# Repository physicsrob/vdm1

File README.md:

This project contains information on the original VDM-1 (Video Display Module) board manufactured by Processor Technologies, as well as a reproduction board referred to as the VDM-2021.

Visit the docs [Here](https://physicsrob.github.io/vdm1)

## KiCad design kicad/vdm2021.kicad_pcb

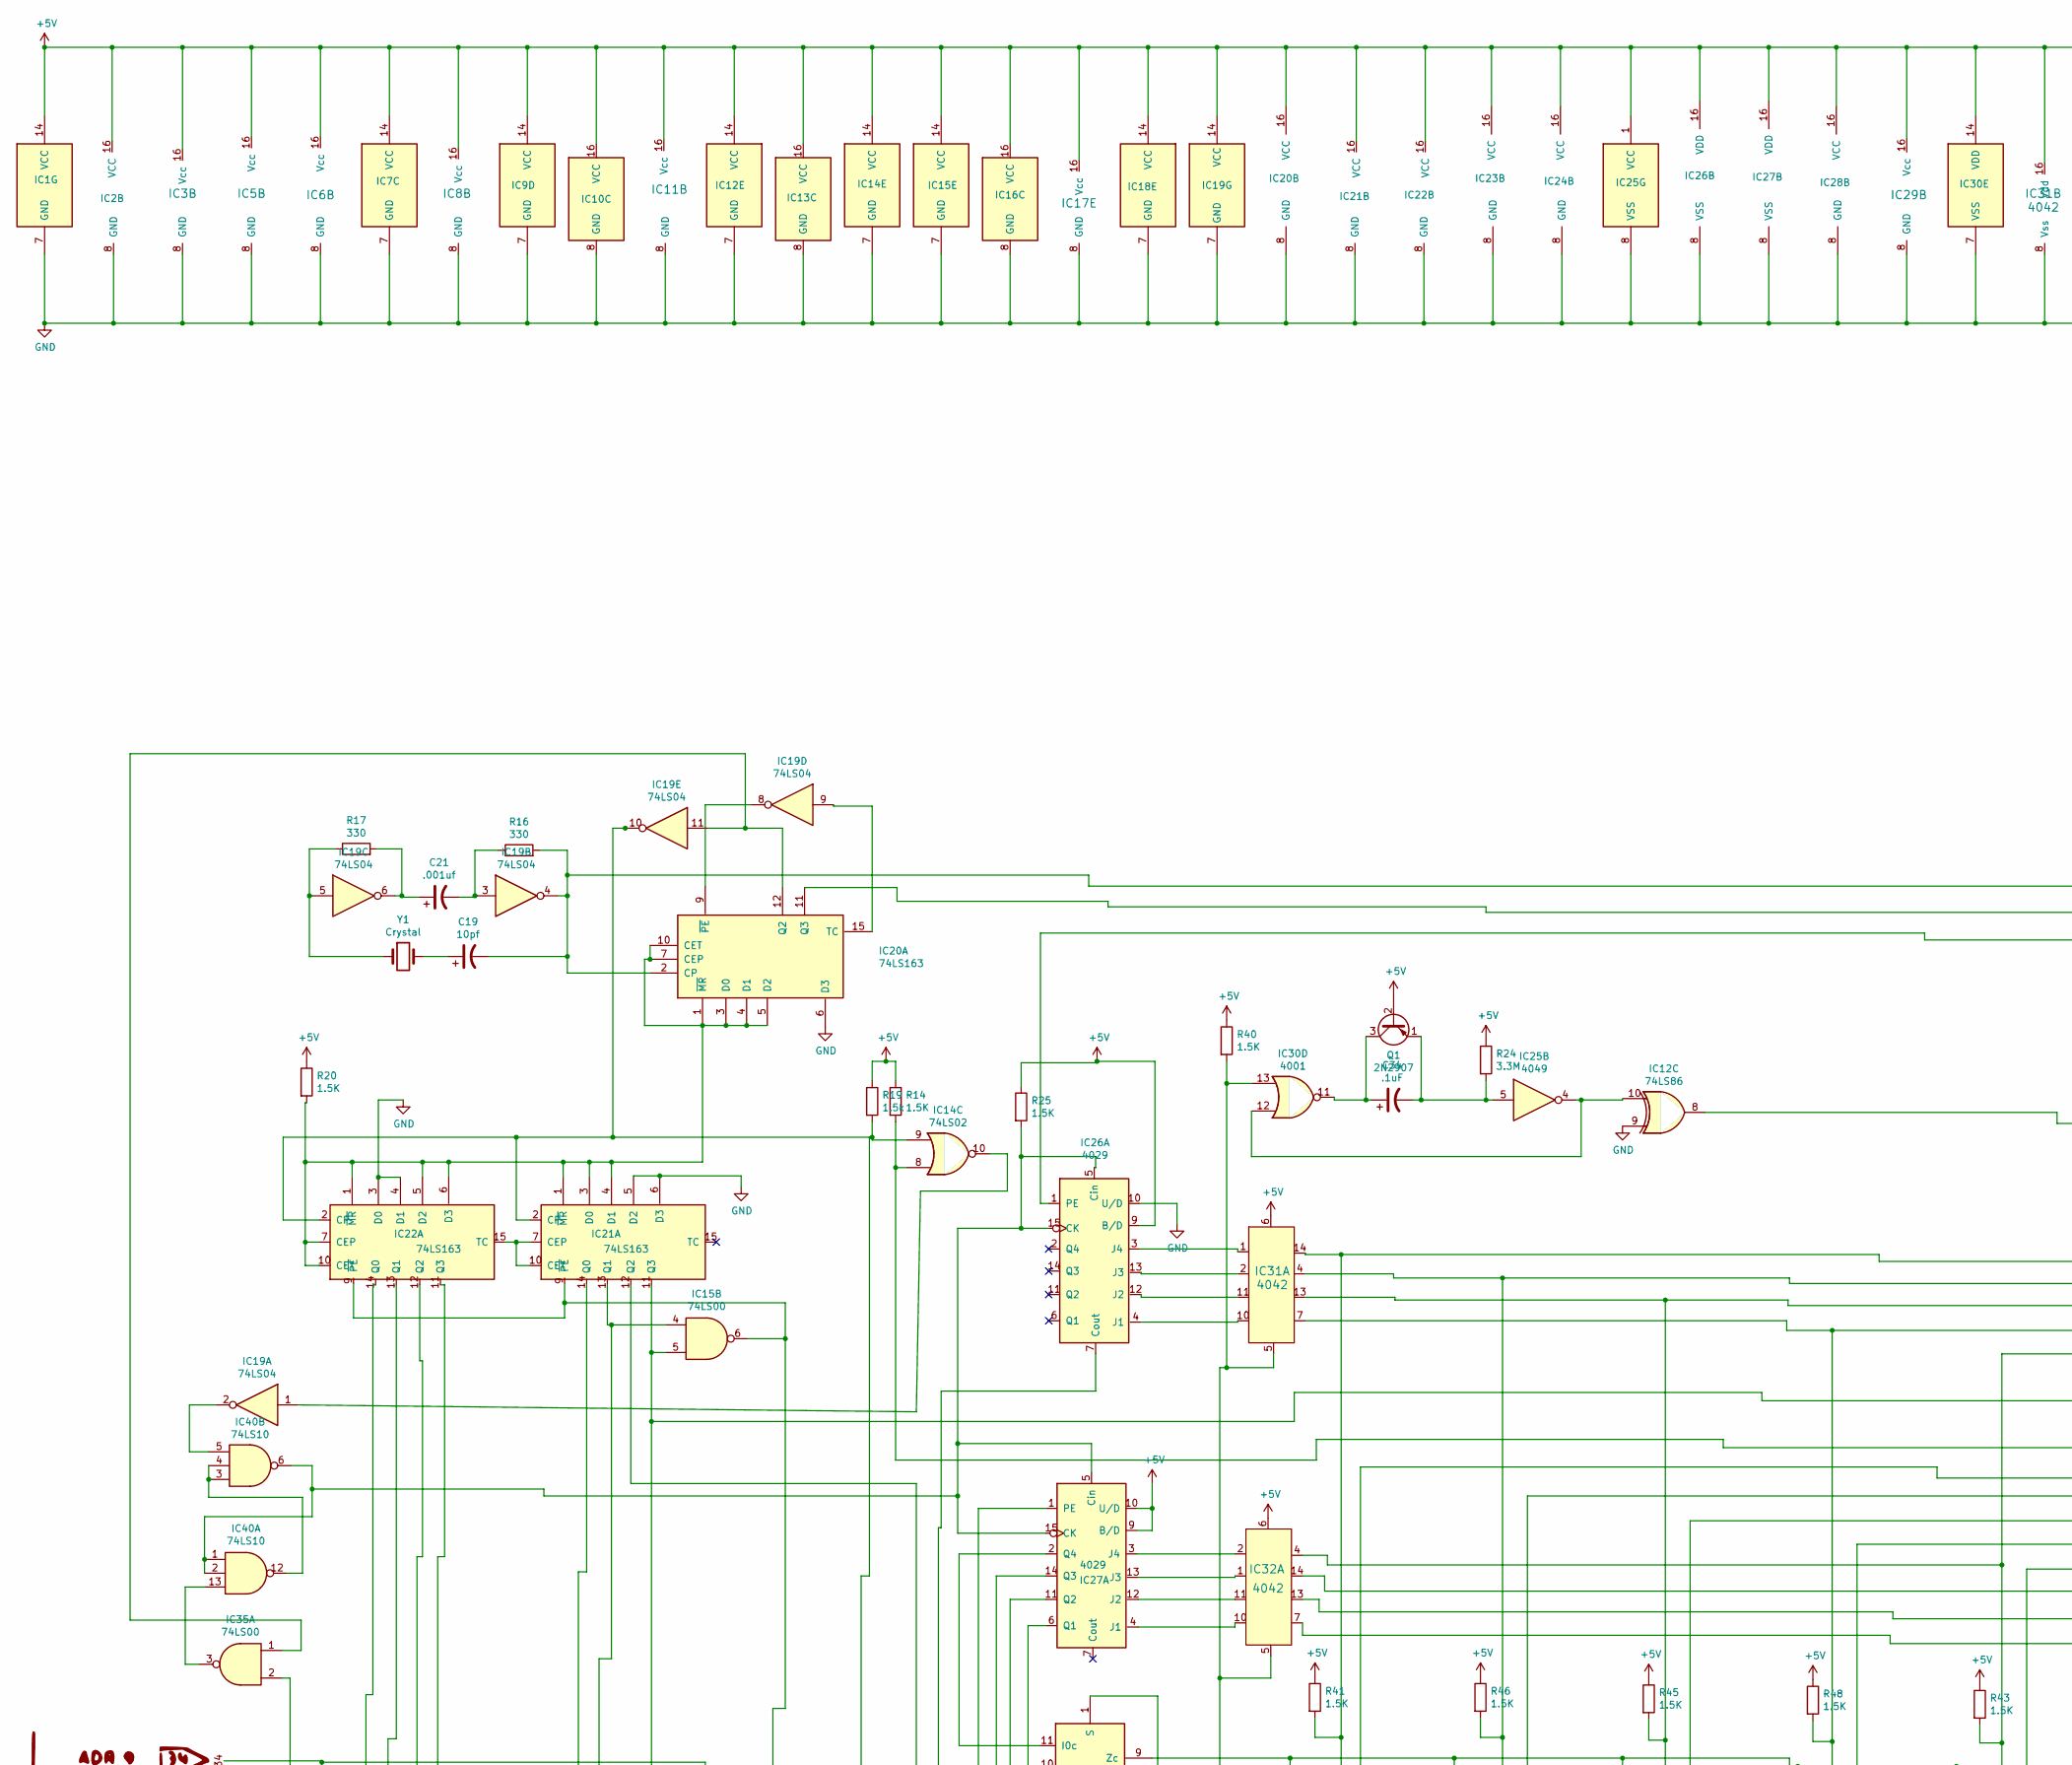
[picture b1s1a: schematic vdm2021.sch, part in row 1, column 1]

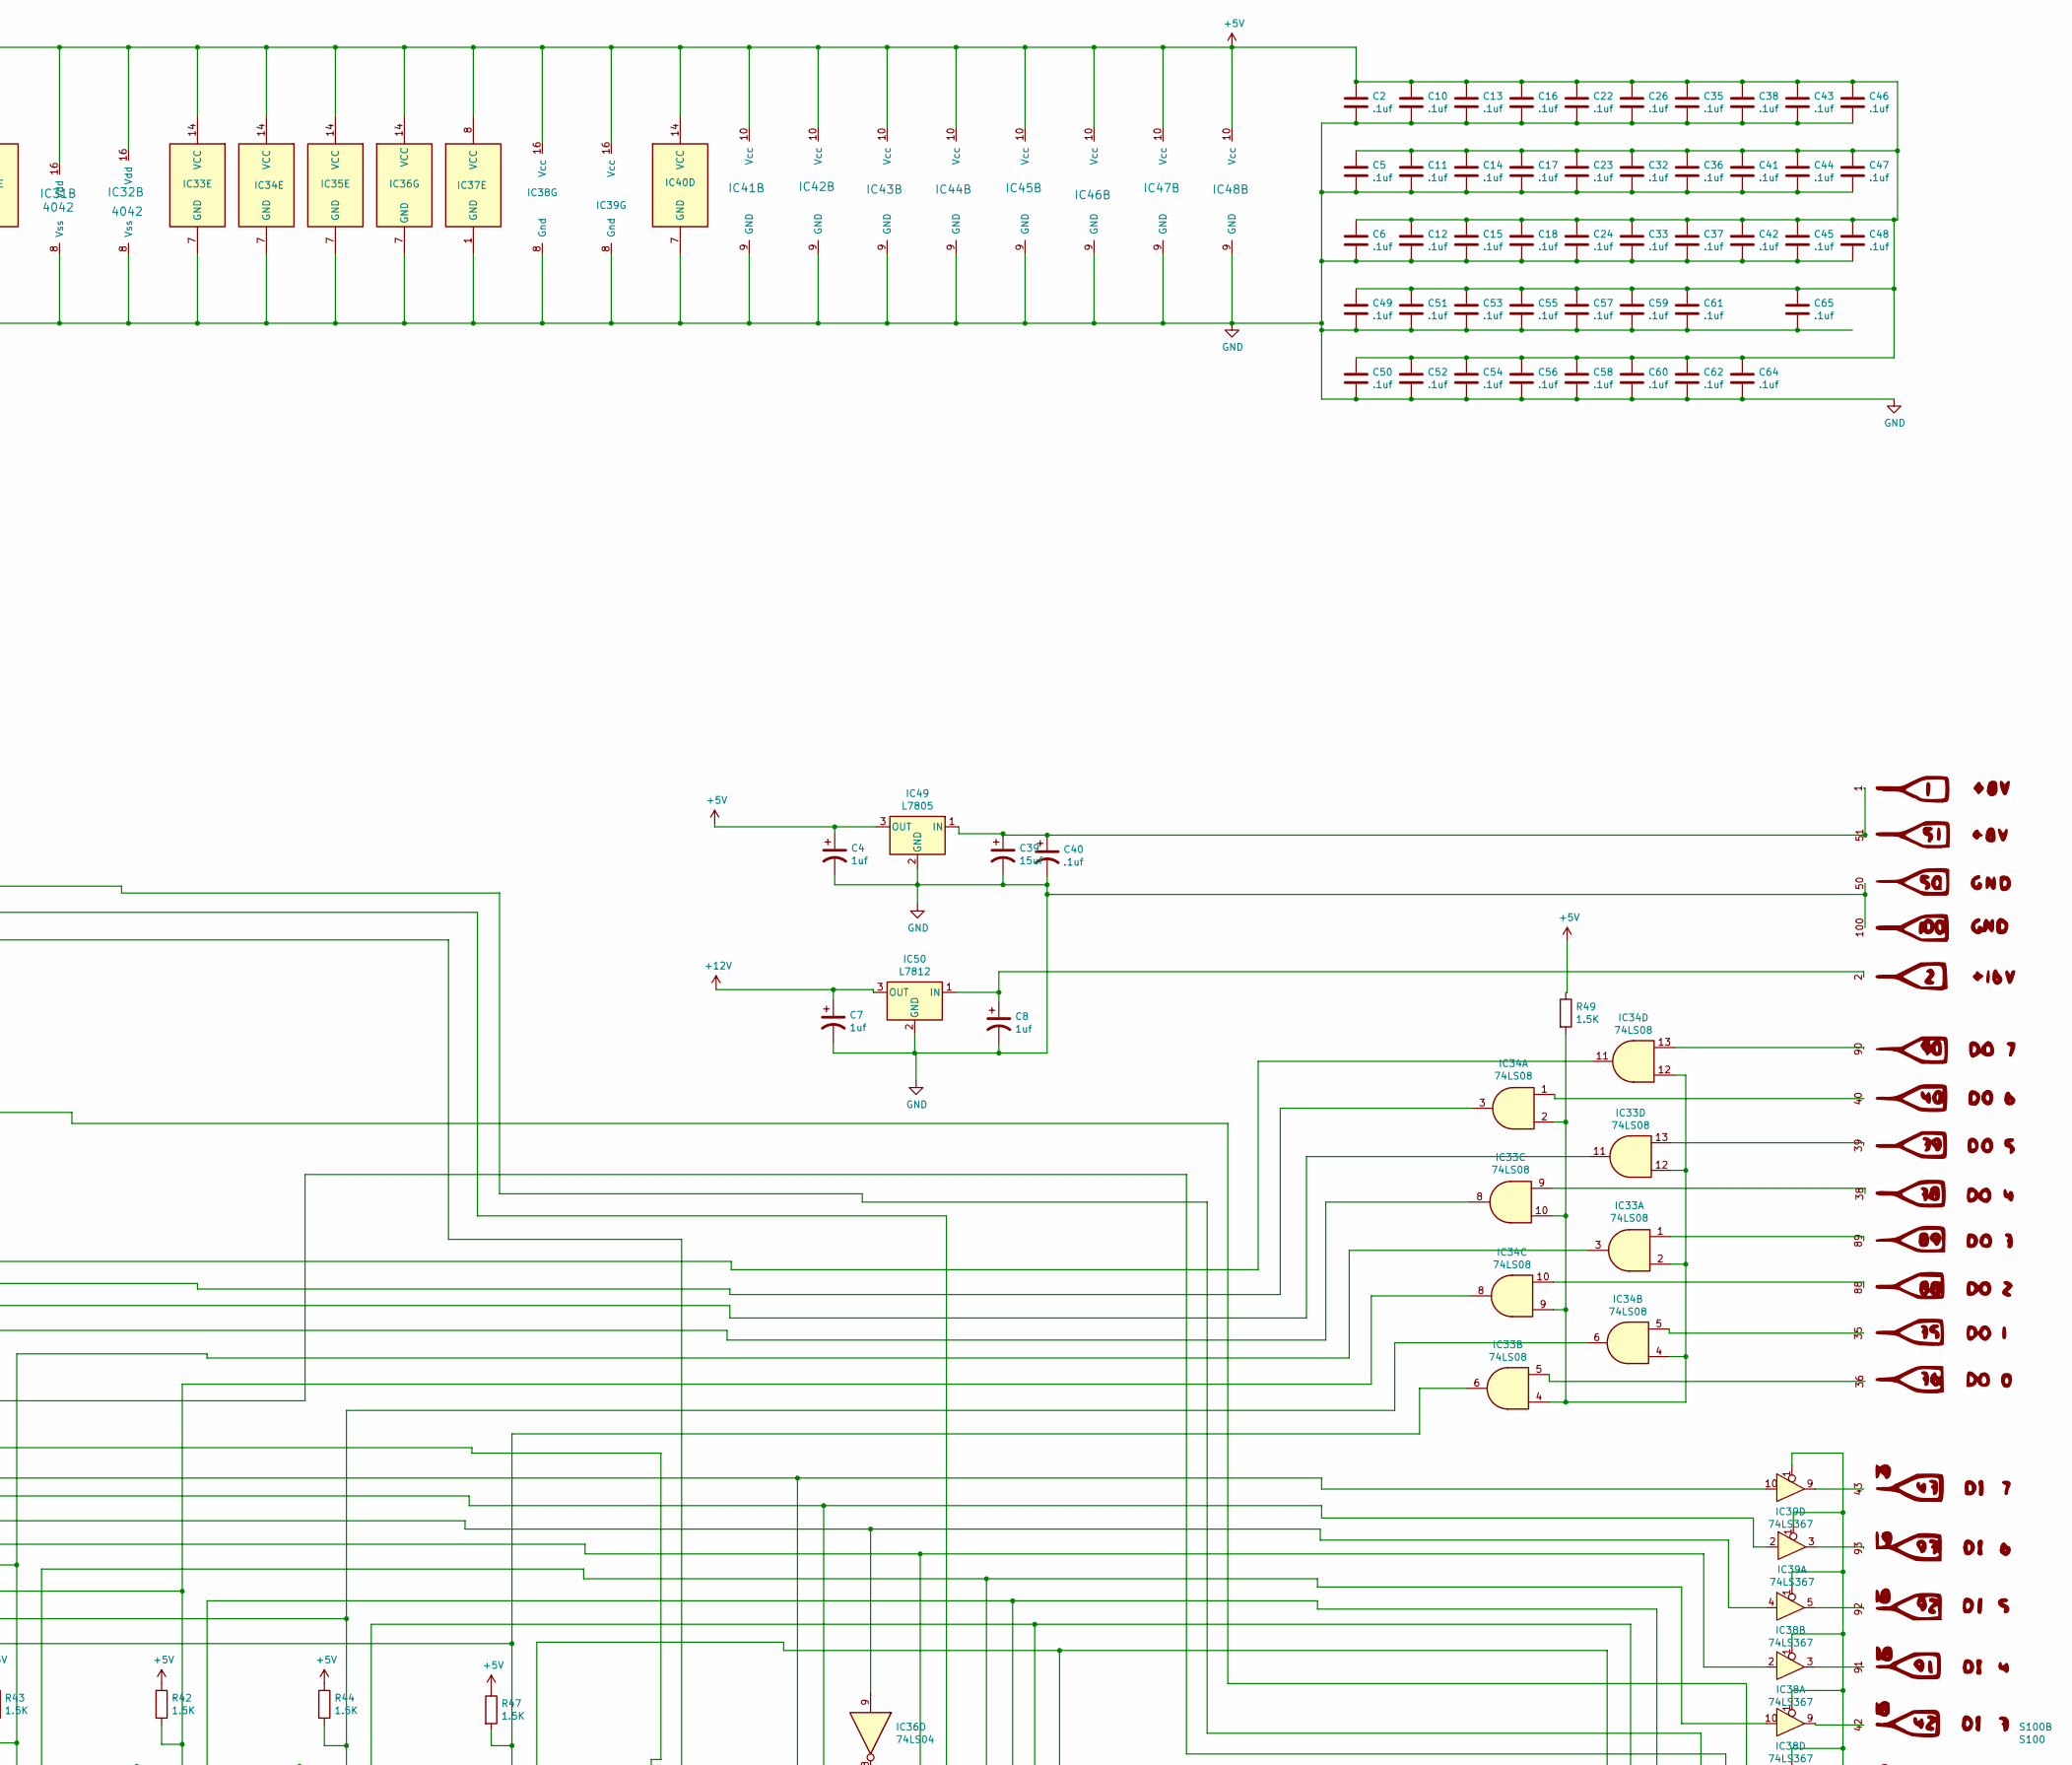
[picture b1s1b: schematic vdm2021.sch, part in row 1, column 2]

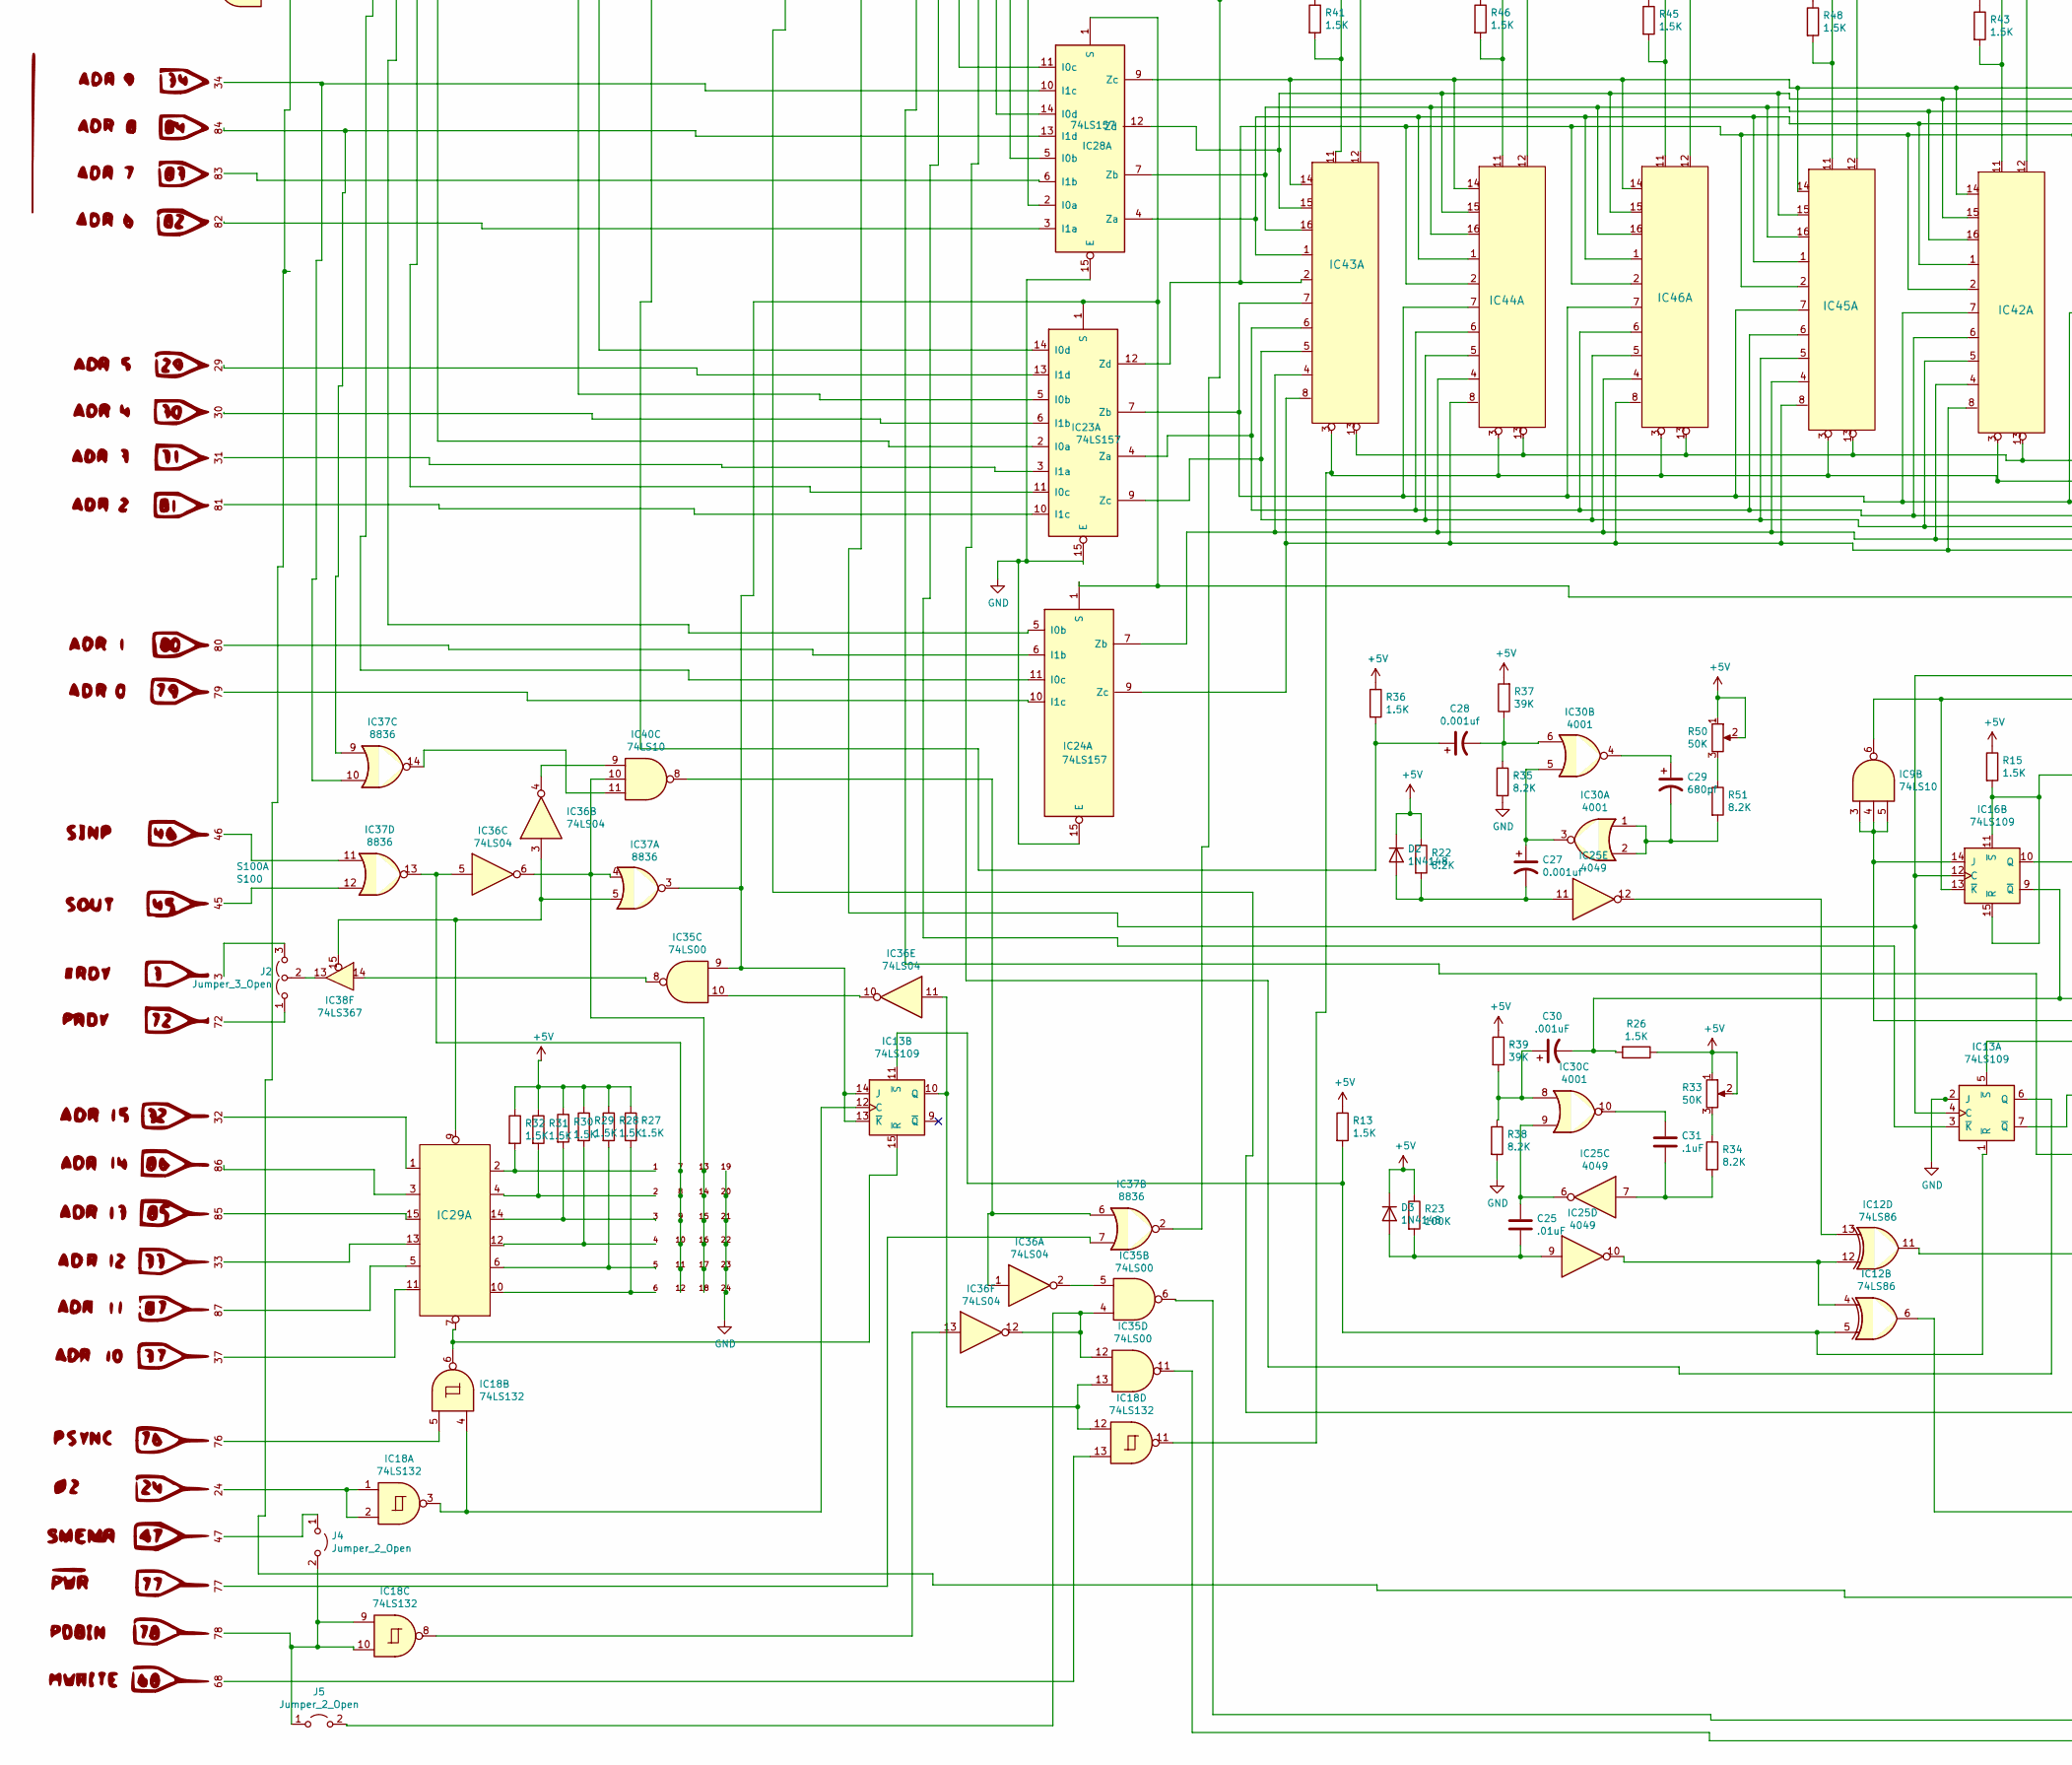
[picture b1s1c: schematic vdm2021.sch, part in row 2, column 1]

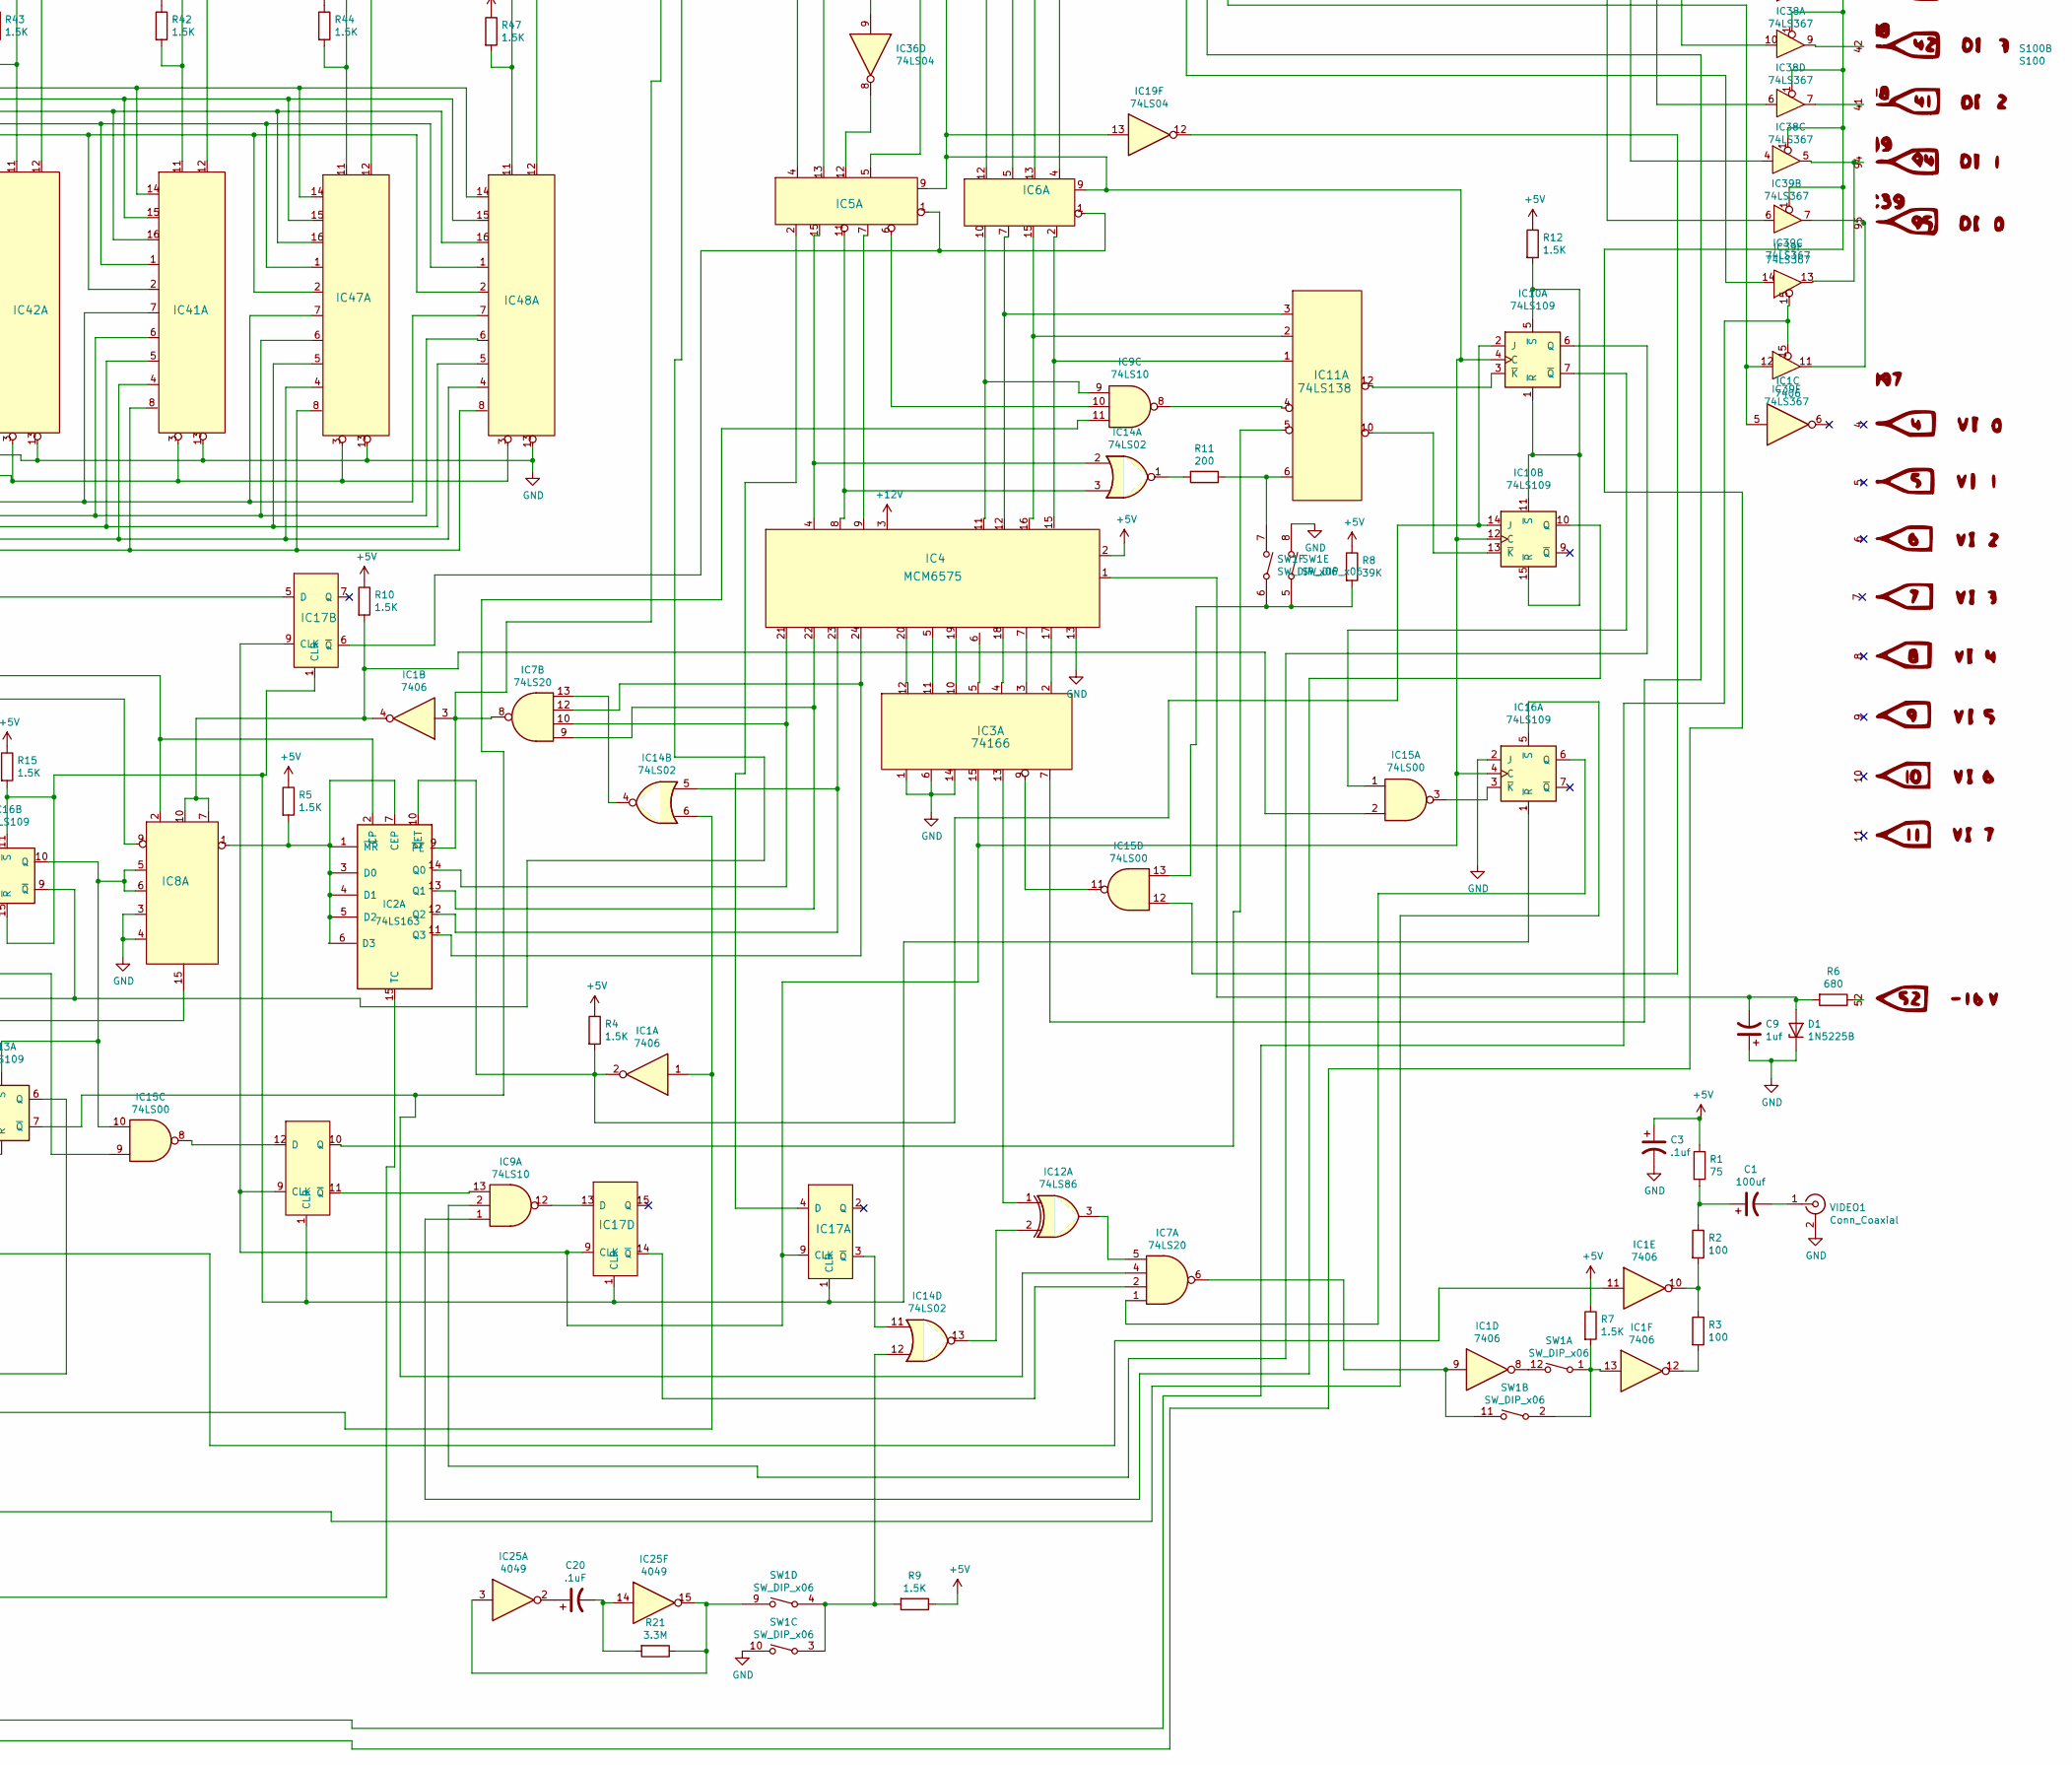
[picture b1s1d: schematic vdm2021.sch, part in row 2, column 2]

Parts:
ADDR1: AddressSelect; ADDR_SELECT
C1: 100uf; CP_Radial_D6.3mm_P2.50mm
C2, C3, C5, C6, C10, C11, C12, C13, C14, C15, C16, C17, C18, C22, C23, C24, C26, C32, C33, C35, C36, C37, C38, C40, C41, C42, C43, C44, C45, C46, C47, C48, C49, C50, C51, C52, C53, C54, C55, C56, C57, C58, C59, C60, C61, C62, C64, C65: .1uf; C_Disc_D6.0mm_W2.5mm_P5.00mm
C4, C7, C8, C9: 1uf; CP_Radial_Tantal_D6.0mm_P2.50mm
C19: 10pf; C_Disc_D6.0mm_W2.5mm_P5.00mm
C20, C31, C34: .1uF; C_Disc_D6.0mm_W2.5mm_P5.00mm
C21: .001uf; C_Disc_D6.0mm_W2.5mm_P5.00mm
C25: .01uF; C_Disc_D6.0mm_W2.5mm_P5.00mm
C27, C28: 0.001uf; C_Disc_D6.0mm_W2.5mm_P5.00mm
C29: 680pf; C_Disc_D3.8mm_W2.6mm_P2.50mm
C30: .001uF; C_Disc_D6.0mm_W2.5mm_P5.00mm
C39: 15uf; CP_Radial_Tantal_D6.0mm_P2.50mm
D1: 1N5225B; D_DO-35_SOD27_P7.62mm_Horizontal
D2, D3: 1N4148; D_DO-35_SOD27_P7.62mm_Horizontal
IC1: 7406; DIP-14_W7.62mm_Socket
IC2, IC20, IC21, IC22: 74LS163; DIP-16_W7.62mm_Socket
IC3: 74166; DIP-16_W7.62mm_Socket
IC4: MCM6575; DIP-24_W15.24mm
IC5, IC6, IC17: 74LS175; DIP-16_W7.62mm_Socket
IC7: 74LS20; DIP-14_W7.62mm_Socket
IC8: 93L16; DIP-16_W7.62mm_Socket
IC9, IC40: 74LS10; DIP-14_W7.62mm_Socket
IC10, IC13, IC16: 74LS109; DIP-16_W7.62mm_Socket
IC11: 74LS138; DIP-16_W7.62mm_Socket
IC12: 74LS86; DIP-14_W7.62mm_Socket
IC14: 74LS02; DIP-14_W7.62mm_Socket
IC15, IC35: 74LS00; DIP-14_W7.62mm_Socket
IC18: 74LS132; DIP-14_W7.62mm_Socket
IC19, IC36: 74LS04; DIP-14_W7.62mm_Socket
IC23, IC24, IC28: 74LS157; DIP-16_W7.62mm_Socket
IC25: 4049; DIP-16_W7.62mm_Socket
IC26, IC27: 4029; DIP-16_W7.62mm_Socket
IC29: DM8131; DIP-16_W7.62mm_Socket
IC30: 4001; DIP-14_W7.62mm_Socket
IC31, IC32: 4042; DIP-16_W7.62mm_Socket
IC33, IC34: 74LS08; DIP-14_W7.62mm_Socket
IC37: 8836; DIP-14_W7.62mm_Socket
IC38, IC39: 74LS367; DIP-16_W7.62mm_Socket
IC41, IC42, IC43, IC44, IC45, IC46, IC47, IC48: 2102; DIP-16_W7.62mm_Socket
IC49: L7805; TO-220-3_Horizontal_TabDown
IC50: L7812; TO-92_Inline_Wide
J2: Jumper_3_Open; PinHeader_1x03_P2.54mm_Vertical
J4, J5: Jumper_2_Open; PinHeader_1x02_P2.54mm_Vertical
Q1: 2N2907; TO-18-3
R1: 75; R_Axial_DIN0207_L6.3mm_D2.5mm_P7.62mm_Horizontal
R2, R3: 100; R_Axial_DIN0207_L6.3mm_D2.5mm_P7.62mm_Horizontal
R4, R5, R7, R9, R10, R12, R13, R14, R15, R20, R25, R26, R27, R28, R29, R30, R31, R32, R36, R40, R41, R42, R43, R44, R45, R46, R47, R48, R49: 1.5K; R_Axial_DIN0207_L6.3mm_D2.5mm_P7.62mm_Horizontal
R6: 680; R_Axial_DIN0207_L6.3mm_D2.5mm_P10.16mm_Horizontal
R8, R37, R39: 39K; R_Axial_DIN0207_L6.3mm_D2.5mm_P7.62mm_Horizontal
R11: 200; R_Axial_DIN0207_L6.3mm_D2.5mm_P7.62mm_Horizontal
R16, R17: 330; R_Axial_DIN0207_L6.3mm_D2.5mm_P7.62mm_Horizontal
R19: 1.5k; R_Axial_DIN0207_L6.3mm_D2.5mm_P7.62mm_Horizontal
R21, R24: 3.3M; R_Axial_DIN0207_L6.3mm_D2.5mm_P7.62mm_Horizontal
R22, R34, R35, R38, R51: 8.2K; R_Axial_DIN0207_L6.3mm_D2.5mm_P7.62mm_Horizontal
R23: 100K; R_Axial_DIN0207_L6.3mm_D2.5mm_P7.62mm_Horizontal
R33, R50: 50K; Potentiometer_ACP_CA9-H2,5_Horizontal
S100: S100; S100_MALE
SW1: SW_DIP_x06; SW_DIP_SPSTx06_Slide_9.78x17.42mm_W7.62mm_P2.54mm
VIDEO1: Conn_Coaxial; bnc-5-16345033
Y1: Crystal; Crystal_HC50_Horizontal

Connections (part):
+5V: C2.1, C3.1, C4.1, C5.1, C6.1, C10.1, C11.1, C12.1, C13.1, C14.1, C15.1, C16.1, C17.1, C18.1, C22.1, C23.1, C24.1, C26.1, C32.1, C33.1, C35.1, C36.1, C37.1, C38.1, C41.1, C42.1, C43.1, C44.1, C45.1, C46.1, C47.1, C48.1, C49.1, C50.1, C51.1, C52.1, C53.1, C54.1, C55.1, C56.1, C57.1, C58.1, C59.1, C60.1, C61.1, C62.1, C64.1, C65.1, D2.1 (K), D3.1 (K), IC1.14 (VCC), IC2.16 (VCC), IC3.16 (Vcc), IC4.2, IC5.16 (Vcc), IC6.16 (Vcc), IC7.14 (VCC), IC8.16 (Vcc), IC9.14 (VCC), IC10.16 (VCC), IC11.16 (Vcc), IC12.14 (VCC), IC13.16 (VCC), IC14.14 (VCC), IC15.14 (VCC), IC16.16 (VCC), IC17.16 (Vcc), IC18.14 (VCC), IC19.14 (VCC), IC20.16 (VCC), IC21.16 (VCC), IC22.16 (VCC), IC23.16 (VCC), IC24.16 (VCC), IC25.1 (VCC), IC26.9 (B/D), IC26.16 (VDD), IC27.9 (B/D), IC27.10 (U/D), IC27.16 (VDD)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
+12V: C7.1, IC4.3, IC50.3 (OUT)
GND: ADDR1.19, ADDR1.20, ADDR1.21, ADDR1.22, ADDR1.23, ADDR1.24, C2.2, C3.2, C4.2, C5.2, C6.2, C7.2, C8.2, C9.1, C10.2, C11.2, C12.2, C13.2, C14.2, C15.2, C16.2, C17.2, C18.2, C22.2, C23.2, C24.2, C26.2, C32.2, C33.2, C35.2, C36.2, C37.2, C38.2, C39.2, C40.2, C41.2, C42.2, C43.2, C44.2, C45.2, C46.2, C47.2, C48.2, C49.2, C50.2, C51.2, C52.2, C53.2, C54.2, C55.2, C56.2, C57.2, C58.2, C59.2, C60.2, C61.2, C62.2, C64.2, C65.2, D1.1 (K), IC1.7 (GND), IC2.8 (GND), IC3.1, IC3.6, IC3.8 (GND), IC3.14, IC4.13, IC5.8 (GND), IC6.8 (GND), IC7.7 (GND), IC8.3, IC8.4, IC8.8 (GND), IC9.7 (GND), IC10.8 (GND), IC11.8 (GND), IC12.7 (GND), IC12.9, IC13.2 (J), IC13.8 (GND)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; also elsewhere on the board
unnamed: ADDR1.1, IC29.2, R32.2
unnamed: ADDR1.2, IC29.4, R31.2
unnamed: ADDR1.3, IC29.14, R30.2
unnamed: ADDR1.4, IC29.12, R29.2
unnamed: ADDR1.5, IC29.6, R28.2
unnamed: ADDR1.6, IC29.10, R27.2
unnamed: ADDR1.7, ADDR1.8, ADDR1.9, ADDR1.10, ADDR1.11, ADDR1.12, IC36.5, IC37.13
unnamed: ADDR1.13, ADDR1.14, ADDR1.15, ADDR1.16, ADDR1.17, ADDR1.18, IC36.6, IC37.4, IC40.10
unnamed: C1.1, R1.2, R2.1
unnamed 12: C1.2, VIDEO1.1 (In); also elsewhere on the board
unnamed: C8.1, IC50.1 (IN), S100.2
unnamed: C9.2, D1.2 (A), IC4.1, R6.2
unnamed: C19.1, Y1.2
unnamed: C19.2, IC3.7, IC19.4, IC20.2 (CP), R16.2
unnamed: C20.1, IC25.2
unnamed: C20.2, IC25.14, R21.2
unnamed: C21.1, IC19.6, R17.2
unnamed: C21.2, IC19.3, R16.1
unnamed: C25.1, IC25.6, IC30.9
unnamed: C25.2, D3.2 (A), IC25.9, R23.2
unnamed: C27.1, IC30.3, IC30.5
unnamed: C27.2, D2.2 (A), IC25.11, R22.2
unnamed: C28.1, IC15.5, IC21.11 (Q3), IC39.14, R36.2
unnamed: C28.2, IC30.6, R35.1, R37.1
unnamed: C29.1, IC30.4
unnamed: C29.2, IC30.1, IC30.2, R51.2
unnamed: C30.1, IC30.8, R38.1, R39.2
unnamed: C30.2, IC16.9 (~Q), IC26.1 (PE), R26.2
unnamed: C31.1, IC30.10
unnamed: C31.2, IC25.7, R34.2
unnamed: C34.1, IC30.11, Q1.3 (C)
unnamed: C34.2, IC25.5, Q1.1 (E), R24.2
unnamed: C39.1, C40.1, IC49.1 (IN), S100.1, S100.51
unnamed: IC1.1, IC14.6, IC15.6, IC21.9 (~PE), IC22.9 (~PE)
unnamed: IC1.2, IC2.10 (CET), IC10.2 (J), IC10.14 (J), R4.2
unnamed: IC1.3, IC2.9 (~PE), IC7.8, IC14.8, R14.2
unnamed: IC1.4, IC8.7, IC8.10, IC15.2, R10.2
unnamed: IC1.5, IC12.8, IC39.12
unnamed: IC1.8, SW1.12
unnamed: IC1.9, IC7.6, SW1.11
unnamed: IC1.10, R2.2, R3.1
unnamed: IC1.11, IC12.11
unnamed: IC1.12, R3.2
unnamed: IC1.13, R7.2, SW1.1, SW1.2
unnamed: IC2.1 (~MR), IC2.3 (D0), IC2.4 (D1), IC2.5 (D2), IC2.6 (D3), IC2.7 (CEP), IC8.1, R5.2
unnamed: IC2.11 (Q3), IC4.24, IC7.12
unnamed: IC2.13 (Q1), IC4.22, IC7.9
unnamed: IC2.14 (Q0), IC4.21, IC7.10
unnamed: IC2.15 (TC), IC35.2
unnamed: IC3.2, IC4.17
unnamed: IC3.3, IC4.7
unnamed: IC3.4, IC4.18
unnamed: IC3.5, IC4.6
unnamed: IC3.10, IC4.19
unnamed: IC3.11, IC4.5
unnamed: IC3.12, IC4.20
unnamed: IC4.9, IC5.7
unnamed: IC4.11, IC6.10, IC9.9
unnamed: IC5.6, IC9.10
unnamed: IC10.1 (~R), IC10.5 (~S), IC10.11 (~S), IC10.15 (~R), R12.2
unnamed: IC10.3 (~K), IC11.12
unnamed: IC9.2, IC10.6 (Q)
unnamed: IC10.7 (~Q), IC15.1
unnamed: IC9.1, IC10.10 (Q)
unnamed: IC3.15, IC5.9, IC6.9, IC10.4 (C), IC10.12 (C), IC16.4 (C), IC17.9 (CLK), IC19.13, IC20.11 (Q3)
unnamed: IC10.13 (~K), IC11.10
unnamed: IC4.15, IC6.2, IC11.1
unnamed: IC4.16, IC6.15, IC11.2
unnamed: IC4.12, IC6.7, IC11.3
unnamed: IC9.8, IC11.4
unnamed: IC11.5, IC17.10 (Q)
unnamed: IC11.6, R11.1, SW1.7
unnamed: IC3.13, IC12.1
unnamed: IC12.2, IC14.13
unnamed: IC7.5, IC12.3
unnamed: IC12.5, IC13.1 (~R), IC13.11 (~S), R13.2
unnamed: IC12.6, IC16.5 (~S)
unnamed: IC12.10, IC25.4, IC30.12
unnamed: IC12.4, IC12.12, IC25.10
unnamed: IC12.13, IC25.12
unnamed: IC13.3 (~K), IC26.7 (Cout)
unnamed: IC2.2 (CP), IC8.2, IC13.4 (C), IC14.9, IC16.12 (C), IC19.10, IC21.2 (CP), IC22.2 (CP), R19.2
unnamed: IC8.5, IC8.6, IC13.5 (~S), IC15.10, IC16.10 (Q)
unnamed: IC13.6 (Q), IC27.1 (PE)
unnamed: IC7.4, IC9.11, IC13.7 (~Q)
unnamed: IC13.10 (Q), IC18.12, IC35.13, IC36.11
unnamed: IC13.12 (C), IC18.3, IC18.4
unnamed: IC13.13 (~K), IC13.14 (J), IC17.5 (D), IC23.1 (S), IC24.1 (S), IC28.1 (S), IC35.9, IC37.3
unnamed: IC13.15 (~R), IC18.6, IC29.7
unnamed: IC14.1, R11.2
unnamed: IC4.4, IC5.15, IC14.2
unnamed: IC4.8, IC5.11, IC14.3
unnamed: IC7.13, IC14.4
unnamed: IC2.12 (Q2), IC4.23, IC14.5
unnamed: IC14.10, IC19.1
unnamed: IC14.11, IC17.3 (~Q)
unnamed: IC14.12, R9.2, SW1.3, SW1.4
unnamed: IC15.3, IC16.3 (~K)
unnamed: IC15.4, IC21.13 (Q1), IC23.14 (I0d)
unnamed: IC15.8, IC17.12 (D)
unnamed: IC15.9, IC21.12 (Q2)
unnamed: IC3.9, IC15.11
unnamed: IC15.12, IC19.12
unnamed: IC15.13, R8.2, SW1.5, SW1.6
unnamed: IC16.1 (~R), IC16.11 (~S), IC16.15 (~R), IC17.1 (CLR), R15.2
unnamed: IC7.1, IC16.6 (Q)
unnamed: IC8.9, IC9.6, IC16.13 (~K)
unnamed: IC8.15, IC9.3, IC9.4, IC9.5, IC16.14 (J)
unnamed: IC5.2, IC17.4 (D)
unnamed: IC5.1, IC6.1, IC17.6 (~Q)
unnamed: IC9.13, IC17.11 (~Q)
unnamed: IC9.12, IC17.13 (D)
unnamed: IC7.2, IC17.14 (~Q)
unnamed: IC18.1, IC18.2, S100.24
unnamed: IC18.5, S100.76
unnamed: IC18.8, IC36.13
unnamed: IC18.9, IC18.10, J4.2 (B), J5.1 (A), S100.78
unnamed: IC18.11, IC41.3, IC42.3, IC43.3, IC44.3, IC45.3, IC46.3, IC47.3, IC48.3
unnamed: IC18.13, S100.68
unnamed: IC19.2, IC40.5
unnamed: IC19.5, R17.1, Y1.1
unnamed: IC19.8, IC20.9 (~PE)
unnamed: IC19.9, IC20.15 (TC)
unnamed: IC19.11, IC20.12 (Q2), IC35.1
unnamed: IC20.1 (~MR), IC20.3 (D0), IC20.4 (D1), IC20.5 (D2), IC20.7 (CEP), IC20.10 (CET), IC21.1 (~MR), IC21.3 (D0), IC21.4 (D1), IC22.1 (~MR), IC22.5 (D2), IC22.6 (D3), IC22.7 (CEP), IC22.10 (CET), R20.2
unnamed: IC21.7 (CEP), IC21.10 (CET), IC22.15 (TC)
unnamed: IC21.14 (Q0), IC23.5 (I0b)
unnamed: IC22.11 (Q3), IC23.2 (I0a)
unnamed: IC22.12 (Q2), IC23.11 (I0c)
unnamed: IC22.13 (Q1), IC24.5 (I0b)
unnamed: IC22.14 (Q0), IC24.11 (I0c)
unnamed: IC23.3 (I1a), S100.31
unnamed: IC23.4 (Za), IC41.6, IC42.6, IC43.6, IC44.6, IC45.6, IC46.6, IC47.6, IC48.6
unnamed: IC23.6 (I1b), S100.30
unnamed: IC23.7 (Zb), IC41.7, IC42.7, IC43.7, IC44.7, IC45.7, IC46.7, IC47.7, IC48.7
unnamed: IC23.9 (Zc), IC41.5, IC42.5, IC43.5, IC44.5, IC45.5, IC46.5, IC47.5, IC48.5
unnamed: IC23.10 (I1c), S100.81
unnamed: IC23.12 (Zd), IC41.2, IC42.2, IC43.2, IC44.2, IC45.2, IC46.2, IC47.2, IC48.2
unnamed: IC23.13 (I1d), S100.29
unnamed: IC24.6 (I1b), S100.80
unnamed: IC24.7 (Zb), IC41.4, IC42.4, IC43.4, IC44.4, IC45.4, IC46.4, IC47.4, IC48.4
unnamed: IC24.9 (Zc), IC41.8, IC42.8, IC43.8, IC44.8, IC45.8, IC46.8, IC47.8, IC48.8
unnamed: IC24.10 (I1c), S100.79
unnamed: IC25.3, IC25.15, R21.1, SW1.9
unnamed: IC26.3 (J4), IC31.1
unnamed: IC26.4 (J1), IC31.10
unnamed: IC26.12 (J2), IC31.11
unnamed: IC26.13 (J3), IC31.2
unnamed: IC26.5 (Cin), IC26.15 (CK), IC27.5 (Cin), IC27.15 (CK), IC40.1, IC40.2, IC40.6, R25.2
unnamed: IC27.2 (Q4), IC28.11 (I0c)
unnamed: IC27.3 (J4), IC32.2
unnamed: IC27.4 (J1), IC32.10
unnamed: IC27.6 (Q1), IC28.2 (I0a)
unnamed: IC27.11 (Q2), IC28.5 (I0b)
unnamed: IC27.12 (J2), IC32.11
unnamed: IC27.13 (J3), IC32.1
unnamed: IC27.14 (Q3), IC28.14 (I0d)
unnamed: IC28.3 (I1a), S100.82
unnamed: IC28.4 (Za), IC41.1, IC42.1, IC43.1, IC44.1, IC45.1, IC46.1, IC47.1, IC48.1
unnamed: IC28.6 (I1b), S100.83
unnamed: IC28.7 (Zb), IC41.16, IC42.16, IC43.16, IC44.16, IC45.16, IC46.16, IC47.16, IC48.16
unnamed: IC28.9 (Zc), IC41.14, IC42.14, IC43.14, IC44.14, IC45.14, IC46.14, IC47.14, IC48.14
unnamed: IC28.10 (I1c), IC37.10, S100.34
unnamed: IC28.12 (Zd), IC41.15, IC42.15, IC43.15, IC44.15, IC45.15, IC46.15, IC47.15, IC48.15
unnamed: IC28.13 (I1d), IC37.9, S100.84
unnamed: IC29.1, S100.32
unnamed: IC29.3, S100.86
unnamed: IC29.5, S100.87
unnamed: IC29.9, IC36.3, IC37.5, IC38.15
unnamed: IC29.11, S100.37
unnamed: IC29.13, S100.33
unnamed: IC29.15, S100.85
unnamed: IC30.13, IC31.5, IC32.5, IC37.2, R40.2
unnamed: IC31.4, IC34.3, IC44.11, R46.2
unnamed: IC31.7, IC33.8, IC45.11, R48.2
unnamed: IC31.13, IC33.11, IC46.11, R45.2
unnamed: IC31.14, IC34.11, IC43.11, R41.2
unnamed: IC32.4, IC33.3, IC42.11, R43.2
unnamed: IC32.7, IC33.6, IC48.11, R47.2
unnamed: IC32.13, IC34.6, IC47.11, R44.2
unnamed: IC32.14, IC34.8, IC41.11, R42.2
unnamed: IC33.1, S100.89
unnamed: IC33.5, S100.36
unnamed: IC33.9, S100.38
unnamed: IC33.2, IC33.4, IC33.10, IC33.12, IC34.2, IC34.4, IC34.9, IC34.12, R49.2
unnamed: IC33.13, S100.39
unnamed: IC34.1, S100.40
unnamed: IC34.5, S100.35
unnamed: IC34.10, S100.88
unnamed: IC34.13, S100.90
unnamed: IC35.3, IC40.13
unnamed: IC35.5, IC36.2
unnamed: IC35.6, IC39.15
unnamed: IC35.8, IC38.14
unnamed: IC35.10, IC36.10
unnamed: IC35.11, IC38.1, IC39.1
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
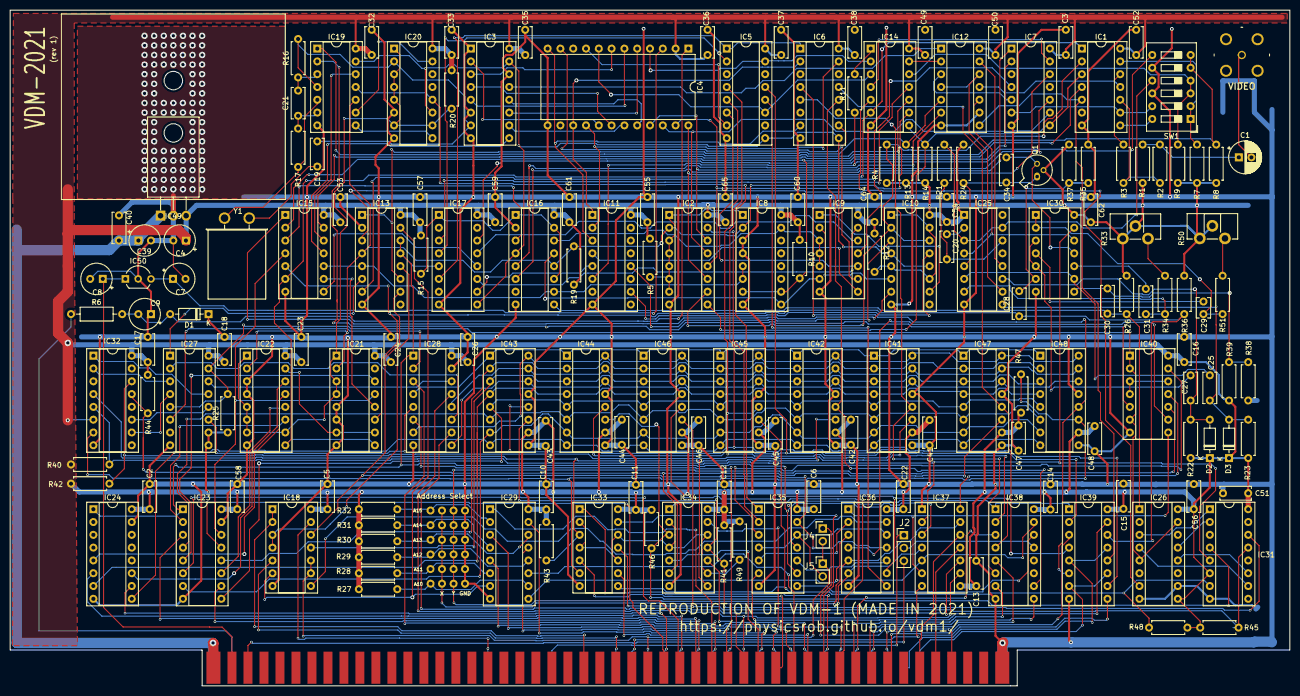
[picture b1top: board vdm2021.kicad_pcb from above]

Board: 2 copper layers, 254.0 x 134.1 mm, 177 parts (0 on the bottom side), 231 nets.

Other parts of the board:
HEAT: Heat Sink; heatsink
VIDEO: Conn_Coaxial; bnc-5-16345033

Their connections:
GND: VIDEO.2; also elsewhere on the board
unnamed 12: VIDEO.1; also elsewhere on the board

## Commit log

2021-06-20 Placement close to done
2021-06-21 Progress
2021-06-21 Very close to fully routed
2021-06-22 Fully routed
2021-06-25 really getting close
2021-06-25 Done
2021-06-25 Fixed s100 connector alignment
2021-06-28 Small redesign for better thermal performance
2021-06-29 Could it be a final version?
2021-08-15 Cleanup structure
2021-08-15 Fix IC36 net in schematic
2021-08-16 Routing updates after last schematic change
2021-08-16 Fixed IC22 load value
2021-08-16 Fixed IC39 Gnd/pwr swap
2021-08-16 Fix Q1 pinout
2021-08-16 Silkscreen tweaks
2021-08-16 Added interactive BOM
2021-08-20 Misc PCB
2021-08-20 Add historical documents
2021-08-20 Added rev silkscreen
2021-08-20 Added gerber
2021-08-22 Added README
2021-08-22 Set theme jekyll-theme-hacker
2021-08-22 No op
2021-08-22 Pages refactor
2021-08-22 Moved history into docs
2021-08-22 Set theme jekyll-theme-slate
2021-08-23 Added board image
2021-08-23 Set theme jekyll-theme-cayman
2021-08-23 Darken image
2021-08-23 Styling
2021-08-23 Style
2021-08-24 Docs WIP
2021-08-25 Doc WIP
2021-08-26 Update pricing
2021-08-27 Fix mistake in docs
2021-08-29 Updated silkscreen URL. Increased footprint size of R6 half watt resistor
2021-08-30 Updated confusing silkscreen for C39
2021-09-07 Assembly directions
2021-09-07 Moved video closer to top-edge. Moved VDM-2021 silkscreen to left edge
2021-09-11 Production Run
2021-11-21 Update assembly
